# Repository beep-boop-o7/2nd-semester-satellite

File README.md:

# 2nd-semester-satellite

## Includes
Put your nonstandard library includes here (the ones you had to install separately)
available in the arduino ide unless otherwise noted

## How to use git (and github)
make sure git is installed.

### Setup

initilize a git instance in the directory(folder) that you want the project stored in
```
git init
```

clone the repo(repository) (copy it to your computer)
```
git clone https://github.com/beep-boop-o7/2nd-semester-satellite.git
```

set repo as origin
```
git remote add origin https://github.com/beep-boop-o7/2nd-semester-satellite.git
```

### Using

make a new branch for the feature you are working on (only do this for new features)
```
git checkout -b subsystem/feature_name
```

add changes to local branch (add all untracked)
```
git add -i
```

commit the changes you have made to the local branch (with a brief description)
```
git commit -m "This is a brief description"
```

push your local branch upstream (to github)
```
git push -u origin subsystem/feature_name
```
after that you go into github to make a merge request to merge your branch into main

to pull the latest changes from main
```
git pull
```

if git complains about unsaved changes
```
git stash
```

a helpful resource 
https://education.github.com/git-cheat-sheet-education.pdf

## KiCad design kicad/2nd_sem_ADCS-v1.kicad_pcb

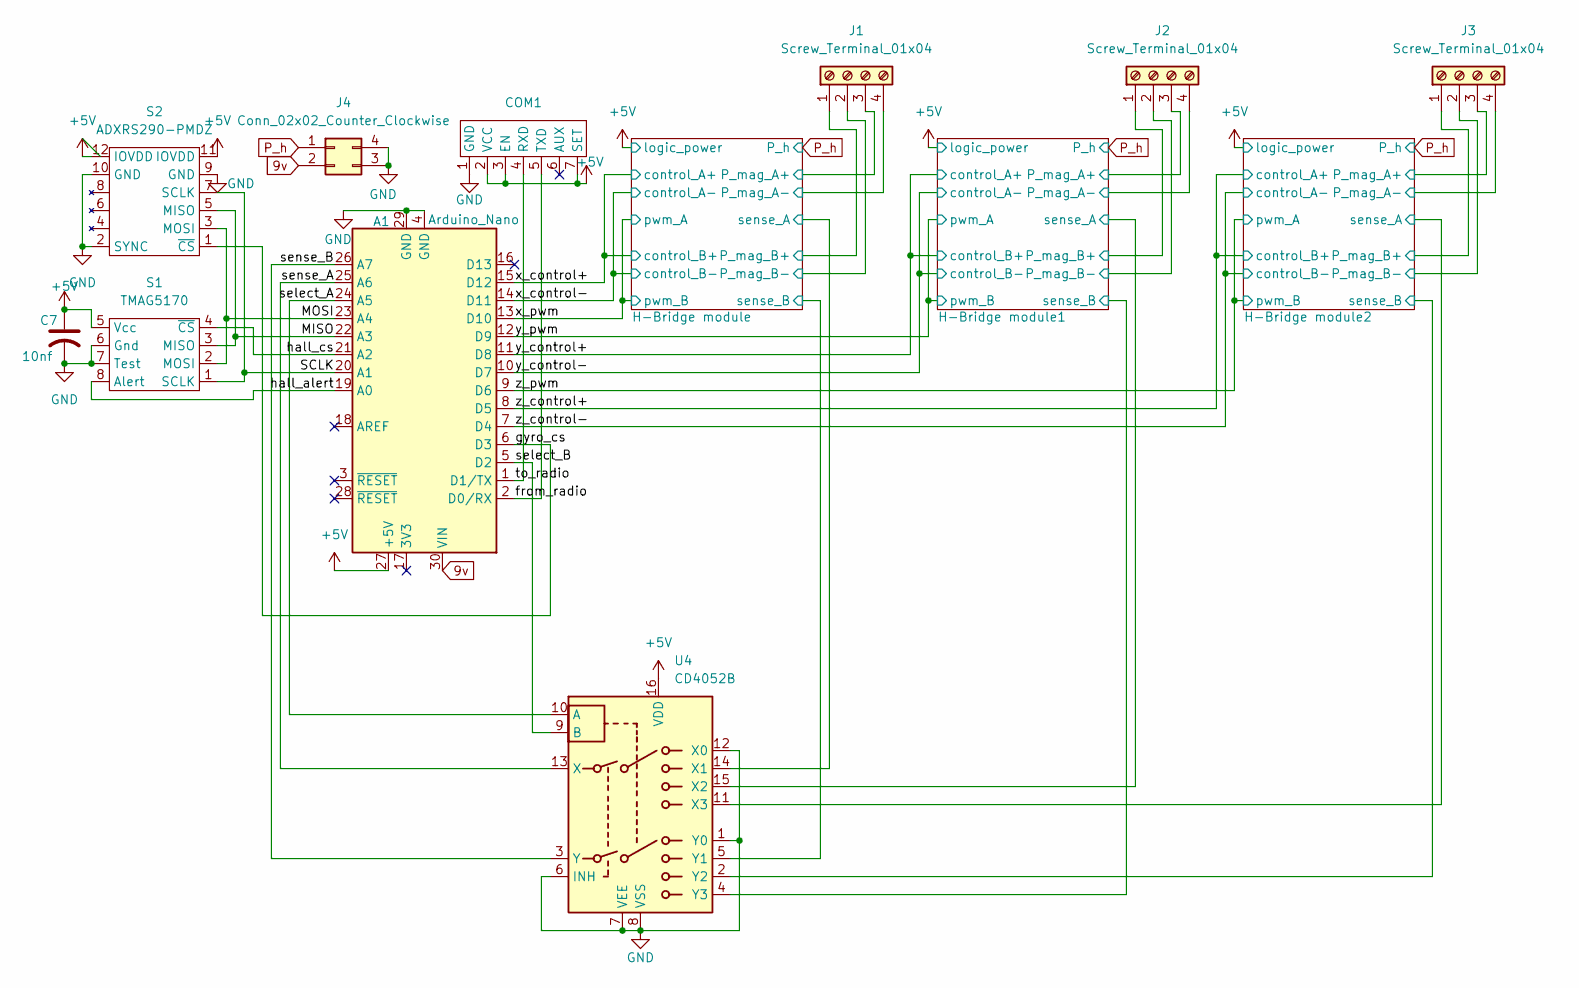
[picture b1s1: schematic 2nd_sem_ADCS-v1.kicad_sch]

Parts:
A1: Arduino_Nano
C7: 10nf; C_0805_2012Metric
COM1: PinHeader_1x07_P2.54mm_Vertical
J1, J2, J3: Screw_Terminal_01x04; TerminalBlock_Xinya_XY308-2.54-4P_1x04_P2.54mm_Horizontal
J4: Conn_02x02_Counter_Clockwise; PinHeader_2x02_P2.54mm_Vertical
S1: TMAG5170; VSSOP-8_3x3mm_P0.65mm
S2: ADXRS290-PMDZ; PinHeader_2x06_P2.54mm_Vertical
U4: CD4052B; DIP-16_W7.62mm

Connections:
9v: A1.30 (VIN), J4.2
+5V: A1.27 (+5V), C7.1, COM1.2 (VCC), COM1.3 (EN), COM1.7 (SET), S1.5 (Vcc), S2.11 (IOVDD), S2.12 (IOVDD), U4.16 (VDD); also elsewhere on the board
/H-Bridge module1/P_mag_A+: J2.3; also elsewhere on the board
/H-Bridge module1/P_mag_A-: J2.4; also elsewhere on the board
/H-Bridge module1/P_mag_B+: J2.1; also elsewhere on the board
/H-Bridge module1/P_mag_B-: J2.2; also elsewhere on the board
/H-Bridge module1/sense_A: U4.15 (X2); also elsewhere on the board
/H-Bridge module1/sense_B: U4.4 (Y3); also elsewhere on the board
/H-Bridge module2/P_mag_A+: J3.3; also elsewhere on the board
/H-Bridge module2/P_mag_A-: J3.4; also elsewhere on the board
/H-Bridge module2/P_mag_B+: J3.1; also elsewhere on the board
/H-Bridge module2/P_mag_B-: J3.2; also elsewhere on the board
/H-Bridge module2/sense_A: U4.11 (X3); also elsewhere on the board
/H-Bridge module2/sense_B: U4.2 (Y2); also elsewhere on the board
/H-Bridge module/P_mag_A+: J1.3; also elsewhere on the board
/H-Bridge module/P_mag_A-: J1.4; also elsewhere on the board
/H-Bridge module/P_mag_B+: J1.1; also elsewhere on the board
/H-Bridge module/P_mag_B-: J1.2; also elsewhere on the board
/H-Bridge module/sense_A: U4.14 (X1); also elsewhere on the board
/H-Bridge module/sense_B: U4.5 (Y1); also elsewhere on the board
/MISO: A1.22 (A3), S1.3 (MISO), S2.5 (MISO)
/MOSI: A1.23 (A4), S1.2 (MOSI), S2.3 (MOSI)
/SCLK: A1.20 (A1), S1.1 (SCLK), S2.7 (SCLK)
/from_radio: A1.2 (D0/RX), COM1.5 (TXD)
/gyro_cs: A1.6 (D3), S2.1 (~CS)
/hall_alert: A1.19 (A0), S1.8 (Alert)
/hall_cs: A1.21 (A2), S1.4 (~CS)
/select_A: A1.24 (A5), U4.10 (A)
/select_B: A1.5 (D2), U4.9 (B)
/sense_A: A1.25 (A6), U4.13 (X)
/sense_B: A1.26 (A7), U4.3 (Y)
/to_radio: A1.1 (D1/TX), COM1.4 (RXD)
/x_control+: A1.15 (D12); also elsewhere on the board
/x_control-: A1.14 (D11); also elsewhere on the board
/x_pwm: A1.13 (D10); also elsewhere on the board
/y_control+: A1.11 (D8); also elsewhere on the board
/y_control-: A1.10 (D7); also elsewhere on the board
/y_pwm: A1.12 (D9); also elsewhere on the board
/z_control+: A1.8 (D5); also elsewhere on the board
/z_control-: A1.7 (D4); also elsewhere on the board
/z_pwm: A1.9 (D6); also elsewhere on the board
GND: A1.4 (GND), A1.29 (GND), C7.2, COM1.1 (GND), J4.3, J4.4, S1.6 (Gnd), S1.7 (Test), S2.2 (SYNC), S2.9 (GND), S2.10 (GND), U4.1 (Y0), U4.6 (INH), U4.7 (VEE), U4.8 (VSS), U4.12 (X0); also elsewhere on the board
P_h: J4.1; also elsewhere on the board

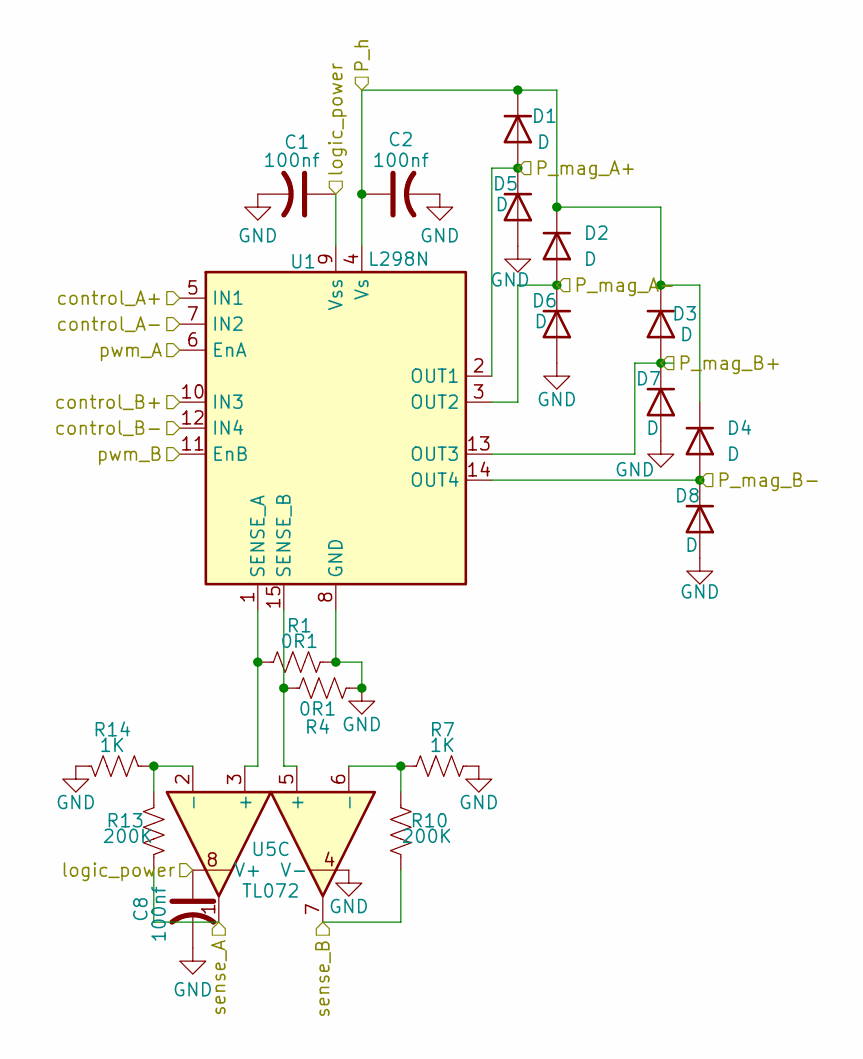
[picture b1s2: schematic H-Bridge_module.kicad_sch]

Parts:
C1, C2, C8: 100nf; C_0805_2012Metric
D1, D2, D3, D4, D5, D6, D7, D8: D; D_SOD-123
R1, R4: 0R1; R_0805_2012Metric
R7, R14: 1K; R_0805_2012Metric
R10, R13: 200K; R_0805_2012Metric
U1: L298N; TO-220-15_P2.54x5.08mm_StaggerOdd_Lead4.58mm_Vertical
U5: TL072; DIP-8_W7.62mm_Socket

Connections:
+5V: C1.1, C8.1, U1.9 (Vss), U5.8 (V+); also elsewhere on the board
/H-Bridge module/P_mag_A+: D1.2 (A), D5.1 (K), U1.2 (OUT1); also elsewhere on the board
/H-Bridge module/P_mag_A-: D2.2 (A), D6.1 (K), U1.3 (OUT2); also elsewhere on the board
/H-Bridge module/P_mag_B+: D3.2 (A), D7.1 (K), U1.13 (OUT3); also elsewhere on the board
/H-Bridge module/P_mag_B-: D4.2 (A), D8.1 (K), U1.14 (OUT4); also elsewhere on the board
/H-Bridge module/sense_A: R13.2, U5.1; also elsewhere on the board
/H-Bridge module/sense_B: R10.2, U5.7; also elsewhere on the board
/x_control+: U1.5 (IN1), U1.10 (IN3); also elsewhere on the board
/x_control-: U1.7 (IN2), U1.12 (IN4); also elsewhere on the board
/x_pwm: U1.6 (EnA), U1.11 (EnB); also elsewhere on the board
GND: C1.2, C2.2, C8.2, D5.2 (A), D6.2 (A), D7.2 (A), D8.2 (A), R1.2, R4.2, R7.2, R14.2, U1.8 (GND), U5.4 (V-); also elsewhere on the board
unnamed: R1.1, U1.1 (SENSE_A), U5.3 (+)
unnamed: R4.1, U1.15 (SENSE_B), U5.5 (+)
unnamed: R13.1, R14.1, U5.2 (-)
unnamed: R7.1, R10.1, U5.6 (-)
P_h: C2.1, D1.1 (K), D2.1 (K), D3.1 (K), D4.1 (K), U1.4 (Vs); also elsewhere on the board

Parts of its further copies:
C3, C4, C5, C6, C9, C10: 100nf; C_0805_2012Metric
D9, D10, D11, D12, D13, D14, D15, D16, D17, D18, D19, D20, D21, D22, D23, D24: D; D_SOD-123
R2, R3, R5, R6: 0R1; R_0805_2012Metric
R8, R9, R16, R18: 1K; R_0805_2012Metric
R11, R12, R15, R17: 200K; R_0805_2012Metric
U2, U3: L298N; TO-220-15_P2.54x5.08mm_StaggerOdd_Lead4.58mm_Vertical
U6, U7: TL072; DIP-8_W7.62mm_Socket

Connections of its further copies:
+5V: C3.1, C5.1, C9.1, C10.1, U2.9 (Vss), U3.9 (Vss), U6.8 (V+), U7.8 (V+); also elsewhere on the board
/H-Bridge module1/P_mag_A+: D9.2 (A), D10.1 (K), U2.2 (OUT1); also elsewhere on the board
/H-Bridge module1/P_mag_A-: D11.2 (A), D12.1 (K), U2.3 (OUT2); also elsewhere on the board
/H-Bridge module1/P_mag_B+: D13.2 (A), D14.1 (K), U2.13 (OUT3); also elsewhere on the board
/H-Bridge module1/P_mag_B-: D15.2 (A), D16.1 (K), U2.14 (OUT4); also elsewhere on the board
/H-Bridge module1/sense_A: R15.2, U6.1; also elsewhere on the board
/H-Bridge module1/sense_B: R11.2, U6.7; also elsewhere on the board
/H-Bridge module2/P_mag_A+: D17.2 (A), D18.1 (K), U3.2 (OUT1); also elsewhere on the board
/H-Bridge module2/P_mag_A-: D19.2 (A), D20.1 (K), U3.3 (OUT2); also elsewhere on the board
/H-Bridge module2/P_mag_B+: D21.2 (A), D22.1 (K), U3.13 (OUT3); also elsewhere on the board
/H-Bridge module2/P_mag_B-: D23.2 (A), D24.1 (K), U3.14 (OUT4); also elsewhere on the board
/H-Bridge module2/sense_A: R17.2, U7.1; also elsewhere on the board
/H-Bridge module2/sense_B: R12.2, U7.7; also elsewhere on the board
/y_control+: U2.5 (IN1), U2.10 (IN3); also elsewhere on the board
/y_control-: U2.7 (IN2), U2.12 (IN4); also elsewhere on the board
/y_pwm: U2.6 (EnA), U2.11 (EnB); also elsewhere on the board
/z_control+: U3.5 (IN1), U3.10 (IN3); also elsewhere on the board
/z_control-: U3.7 (IN2), U3.12 (IN4); also elsewhere on the board
/z_pwm: U3.6 (EnA), U3.11 (EnB); also elsewhere on the board
GND: C3.2, C4.2, C5.2, C6.2, C9.2, C10.2, D10.2 (A), D12.2 (A), D14.2 (A), D16.2 (A), D18.2 (A), D20.2 (A), D22.2 (A), D24.2 (A), R2.2, R3.2, R5.2, R6.2, R8.2, R9.2, R16.2, R18.2, U2.8 (GND), U3.8 (GND), U6.4 (V-), U7.4 (V-); also elsewhere on the board
unnamed: R2.1, U2.1 (SENSE_A), U6.3 (+)
unnamed: R5.1, U2.15 (SENSE_B), U6.5 (+)
unnamed: R3.1, U3.1 (SENSE_A), U7.3 (+)
unnamed: R6.1, U3.15 (SENSE_B), U7.5 (+)
unnamed: R15.1, R16.1, U6.2 (-)
unnamed: R8.1, R11.1, U6.6 (-)
unnamed: R17.1, R18.1, U7.2 (-)
unnamed: R9.1, R12.1, U7.6 (-)
P_h: C4.1, C6.1, D9.1 (K), D11.1 (K), D13.1 (K), D15.1 (K), D17.1 (K), D19.1 (K), D21.1 (K), D23.1 (K), U2.4 (Vs), U3.4 (Vs); also elsewhere on the board

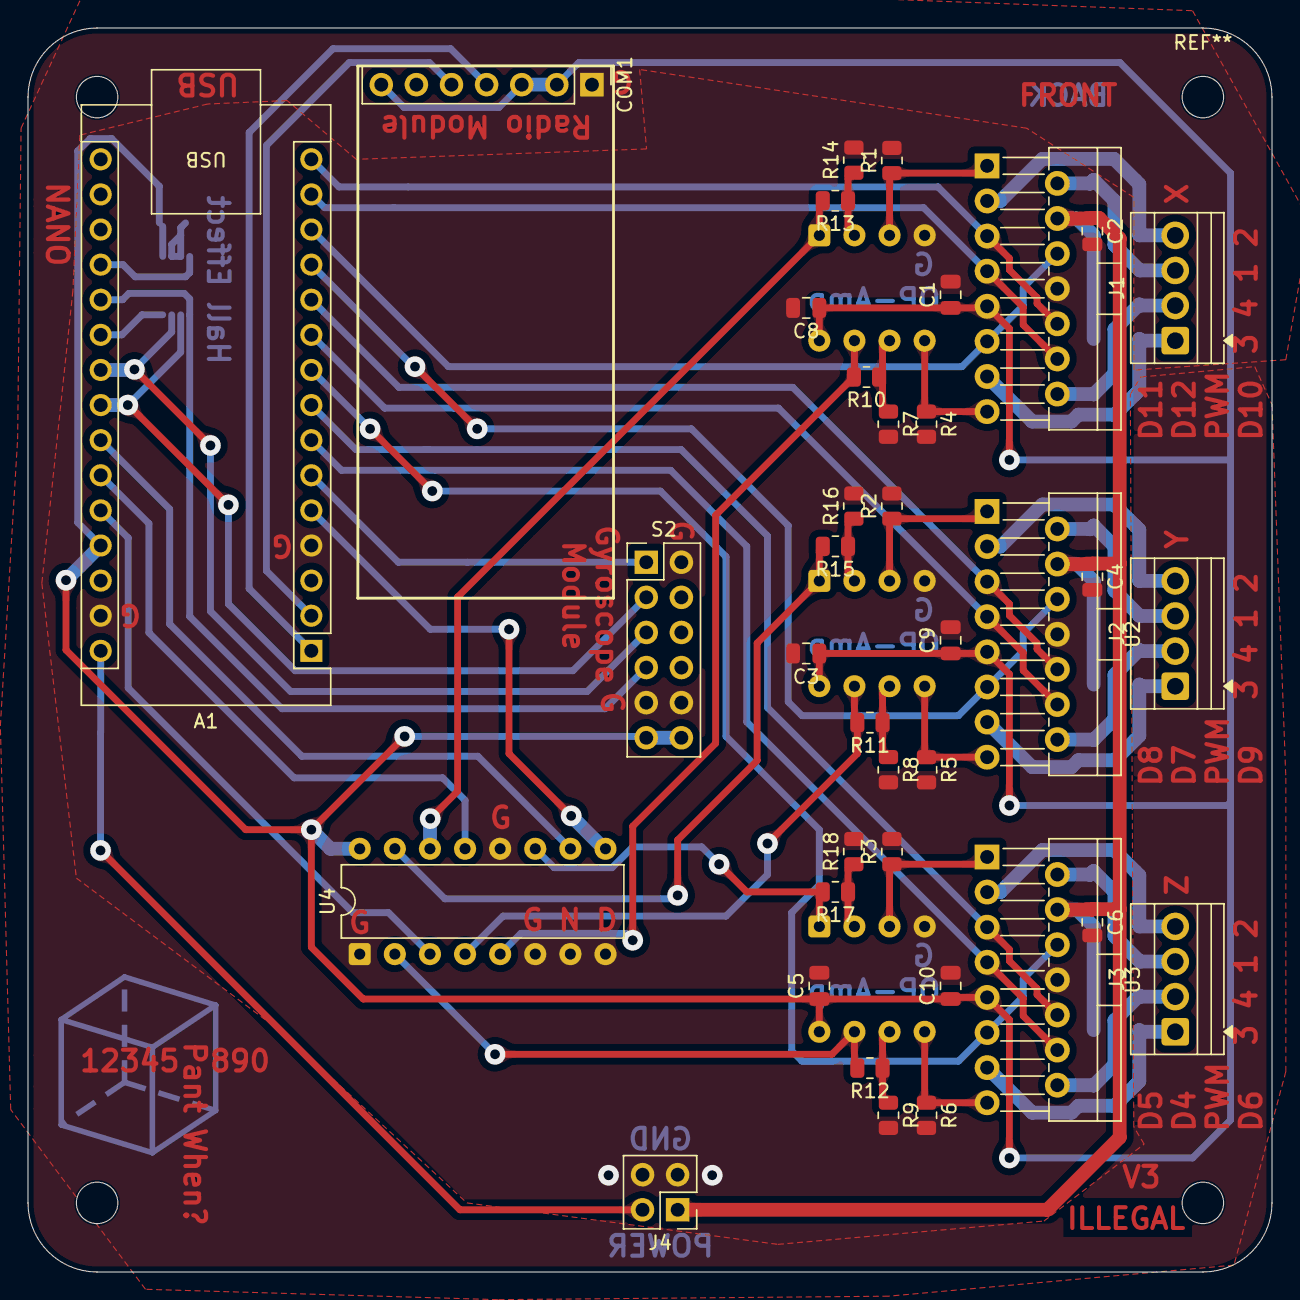
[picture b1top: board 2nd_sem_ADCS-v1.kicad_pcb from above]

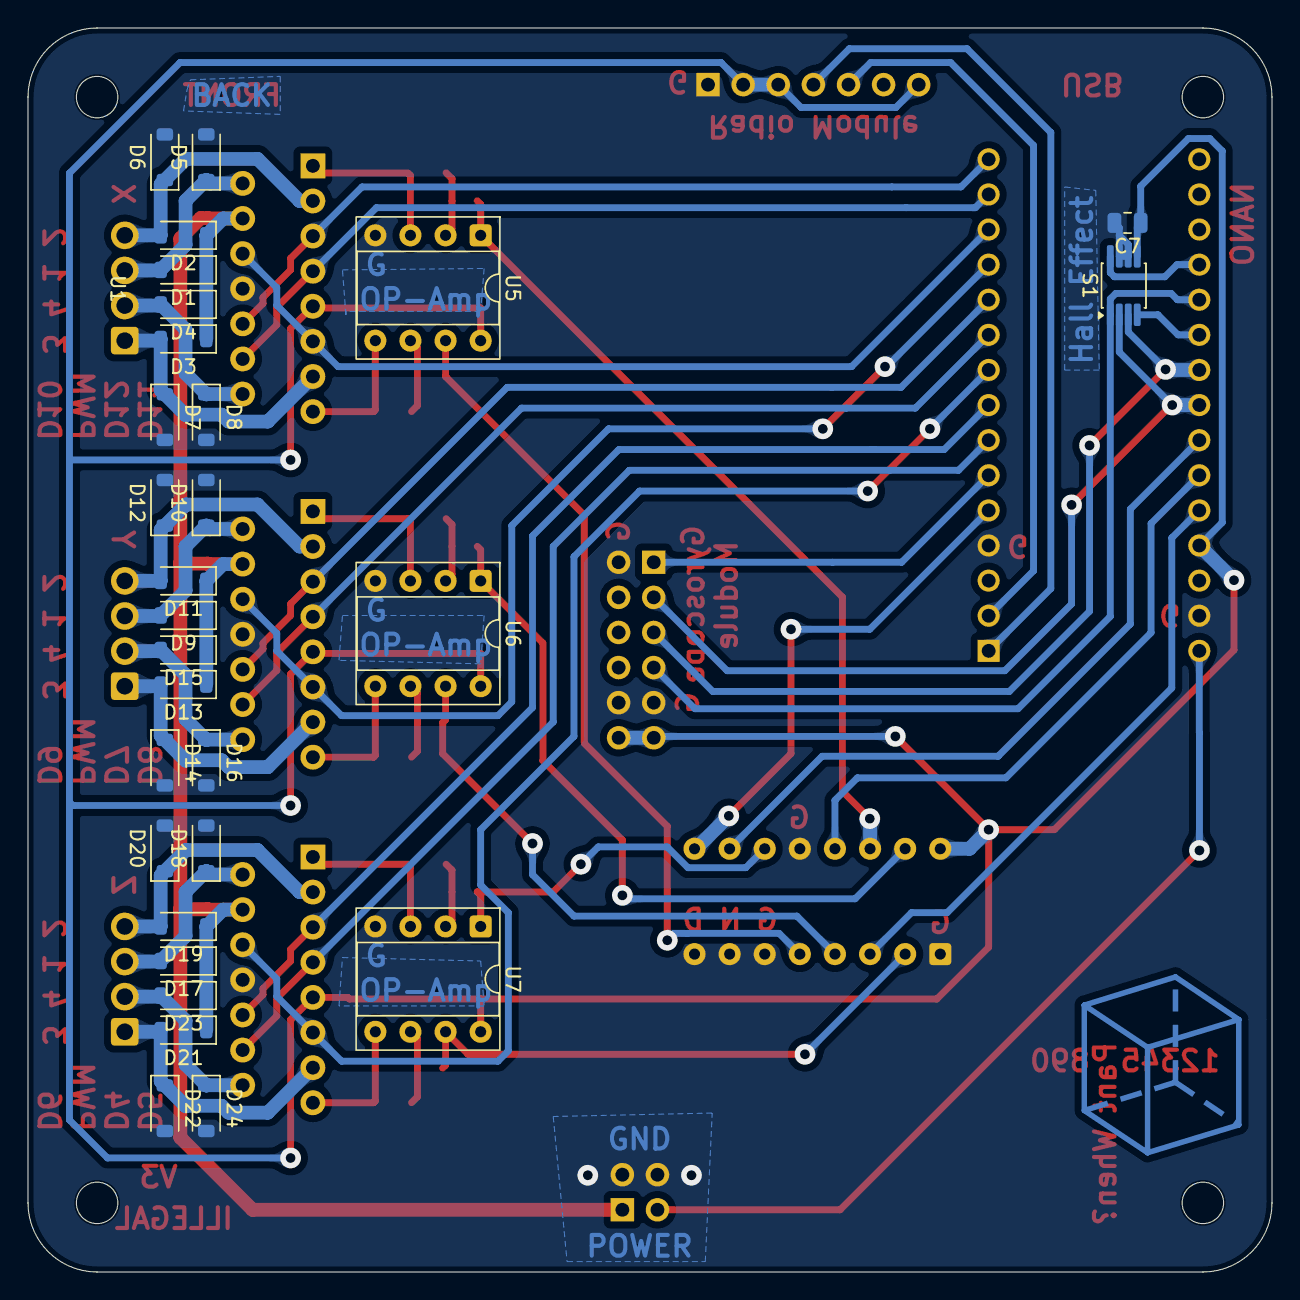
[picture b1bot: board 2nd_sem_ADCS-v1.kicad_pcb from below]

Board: 2 copper layers, 90.0 x 90.0 mm, 67 parts (29 on the bottom side), 55 nets.

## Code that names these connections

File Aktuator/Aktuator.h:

#ifndef Aktuator
#define Aktuator

#include <Arduino.h>
#include <math.h>

typedef struct{
    float x, y, z;
} aktuator_data;

/**
 * @brief fast stops magnetorquers by grounding both side of the H-bridge
 */
void Stop_Magnetorquers();

/**
 * @brief sets current flowing through each axis to (max_mA * control_vector.(x,y,z) * 2)
 * @param control_vector 3d vector with values between 1 and -1 representing % strength
 */
void Command_Magnetorquers(aktuator_data control_vector);

/**
 * @brief sets all pins for use in other functions and sets max mA per coil
 * @param x_A A pin connected to x
 * @param y_A A pin connected to y
 * @param z_A A pin connected to z
 * @param select_A A pin connected to select
 * @param sens_A A pin connected to sens
 * @param x_B B pin connected to x
 * @param y_B B pin connected to y
 * @param z_B B pin connected to z
 * @param select_B B pin connected to select
 * @param sens_B B pin connected to sens
 * @param x_PWM PWM pin connected to x
 * @param y_PWM PWM pin connected to y
 * @param z_PWM PWM pin connected to z
 * @param max_mA max milliAmpere you want to pull on each coil (2 coils per axis)
 */
void Init_Magnetorquers(uint8_t x_A, uint8_t x_B, uint8_t x_PWM, uint8_t y_A, uint8_t y_B, uint8_t y_PWM, uint8_t z_A, uint8_t z_B, uint8_t z_PWM, uint8_t select_A, uint8_t select_B, uint8_t sens_A, uint8_t sens_B, float max_mA);

#endif

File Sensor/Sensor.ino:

#include "Gyro.h"
#include "hall_effect_sensor.h"
#include "rt_spi.h"
#include <krnl.h>
#include <Arduino.h>

#define SPI_CLOCK A0
#define SPI_MOSI A1
#define SPI_MISO A2
#define HALL_CS_PIN A3
#define HALL_ALERT_PIN A4
#define GYRO_CS_PIN A5

#define STK 150
char t1[STK], t2[STK], t3[STK];

struct k_t *pTask_Hall, *pTask_Gyro, *pTask_Print;

struct k_t *Timed_Sem1, *Timed_Sem2, *Timed_Sem3;

hall_sensor_data Hall_Data_Queue[4];

gyro_sensor_data Gyro_Data_Queue[4];

struct k_msg_t *Queue_Hall, *Queue_Gyro;

void Task_Hall() {
    hall_sensor_data hall_data;

    k_set_sem_timer(Timed_Sem1, 100);

    pinMode(HALL_CS_PIN, OUTPUT);
    pinMode(HALL_ALERT_PIN, OUTPUT);
	digitalWrite(HALL_CS_PIN, HIGH);
    digitalWrite(HALL_ALERT_PIN, HIGH);

    Init_TMAG(HALL_CS_PIN);

    while (1) {
        k_wait(Timed_Sem1, 0);

        Read_TMAG(&hall_data, HALL_CS_PIN, HALL_ALERT_PIN);

        k_send(Queue_Hall, &hall_data);
    }
}

void Task_Gyro() {
    gyro_sensor_data gyro_data;

    k_set_sem_timer(Timed_Sem2, 50);

    pinMode(GYRO_CS_PIN, OUTPUT);
    digitalWrite(GYRO_CS_PIN, HIGH);

    Gyro_Setup(GYRO_CS_PIN);

    while (1) {
        k_wait(Timed_Sem2, 0);

        Update_Gyro(&gyro_data, GYRO_CS_PIN);

        k_send(Queue_Gyro, &gyro_data);
    }
}

void Task_Print() {
    hall_sensor_data hall_data, hall_tmp;
    gyro_sensor_data gyro_data, gyro_tmp;
    int missed;

    hall_data.x = 0;
    hall_data.y = 0;
    hall_data.z = 0;

    gyro_data.Angle = 0;
    gyro_data.rate = 0;

    k_set_sem_timer(Timed_Sem3, 1000);

    while (1) {
        if(k_receive(Queue_Hall, &hall_tmp, -1, &missed) != -1) {
            hall_data = hall_tmp;
        }
        if(k_receive(Queue_Gyro, &gyro_tmp, -1, &missed) != -1) {
            gyro_data = gyro_tmp;
        }
        if(k_wait(Timed_Sem3, -1) > 0) {
            Serial.println("Hall Data");
            Serial.print("x: ");
            Serial.print(hall_data.x);
            Serial.print(" y: ");
            Serial.print(hall_data.y);
            Serial.print(" z: ");
            Serial.println(hall_data.z);
            Serial.println("Gyro Data");
            Serial.print("angle: ");
            Serial.print(gyro_data.Angle);
            Serial.print(" rate: ");
            Serial.println(gyro_data.rate);
        }
    }
}

void setup() {
	Serial.begin(115200);
    while (!Serial);    
	
	Serial.println("just bef init part");
	
	k_init(3, 4, 2);
	//     |  |  |-- num of msg Queues (2) hall effect, gyroscope
	//     |  |----- num of semaphores (4) SPI, timer 1-2-3
	//     |------------- num of tasks (3) hall, gyro, print
	
	Queue_Hall = k_crt_send_Q(4, sizeof(hall_sensor_data),  Hall_Data_Queue);  // 4 elements of size
	Queue_Gyro = k_crt_send_Q(4, sizeof(gyro_sensor_data),  Gyro_Data_Queue);  // 4 elements of size

	pTask_Hall = k_crt_task(Task_Hall, 10, t1, STK);
	pTask_Gyro = k_crt_task(Task_Gyro, 10 , t2, STK);
    pTask_Print = k_crt_task(Task_Print, 20, t3, STK);

	Timed_Sem1 = k_crt_sem(0, 1); // 0: start value, 1: max value (clipping)
	Timed_Sem2 = k_crt_sem(0, 1); // 0: start value, 1: max value (clipping)
    Timed_Sem3 = k_crt_sem(0, 1); // 0: start value, 1: max value (clipping)

    Init_SPI(SPI_MOSI, SPI_MISO, SPI_CLOCK);

	Serial.println("just bef k_start");
	
	k_start(); /* start krnl timer speed 1 milliseconds*/
	
	Serial.println("If you see this then krnl crashed :-(");
}

void loop() {}

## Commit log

2026-04-16 adding folders
2026-04-20 Prototype 1
2026-04-20 Prototype 1 fixed
2026-04-20 Fixed Prototype 1 fixed
2026-04-21 add SPI interface
2026-04-28 This is a brief description
2026-04-28 Add files via upload
    Nu virker y-aksen
2026-04-28 Add gyroSetup function declaration
2026-04-28 Add CS_PIN definition to Gyro.h
2026-04-29 Add documentation for gyroSetup function
    Lavede kommentar
2026-04-29 move hall code to proper directory
2026-04-29 rename
2026-04-29 add test file
2026-04-29 bugfix: can compile
2026-04-29 small fix
2026-04-29 !!! VERY IMPORTANT !!!
2026-04-30 now works
2026-04-30 why?
2026-04-30 Create Gyro_kode_og_wireless_transmission.ino
    gyro test kode med esp32
2026-05-04 Add additional SPI write for Gyro filter mode
2026-05-04 basic mag control algorithm
2026-05-05 stop using next_command to start aditional conversions
2026-05-11 convert to library
2026-05-13 radio working
2026-05-15 add kicad files for v3 of circit
2026-05-17 actuator code
2026-05-17 actuator code (for real this time)
2026-05-17 actuator code (for real this time (with .h))
2026-05-18 restructuring and final test code? hopefully
2026-05-18 make PID mork more corectly
2026-05-19 print gyro data
2026-05-19 make better
2026-05-19 trobbleshot
2026-05-19 trobbledead
2026-05-19 trobbleundead
2026-05-20 working now
2026-05-20 trobbleunundead
2026-05-20 new1
